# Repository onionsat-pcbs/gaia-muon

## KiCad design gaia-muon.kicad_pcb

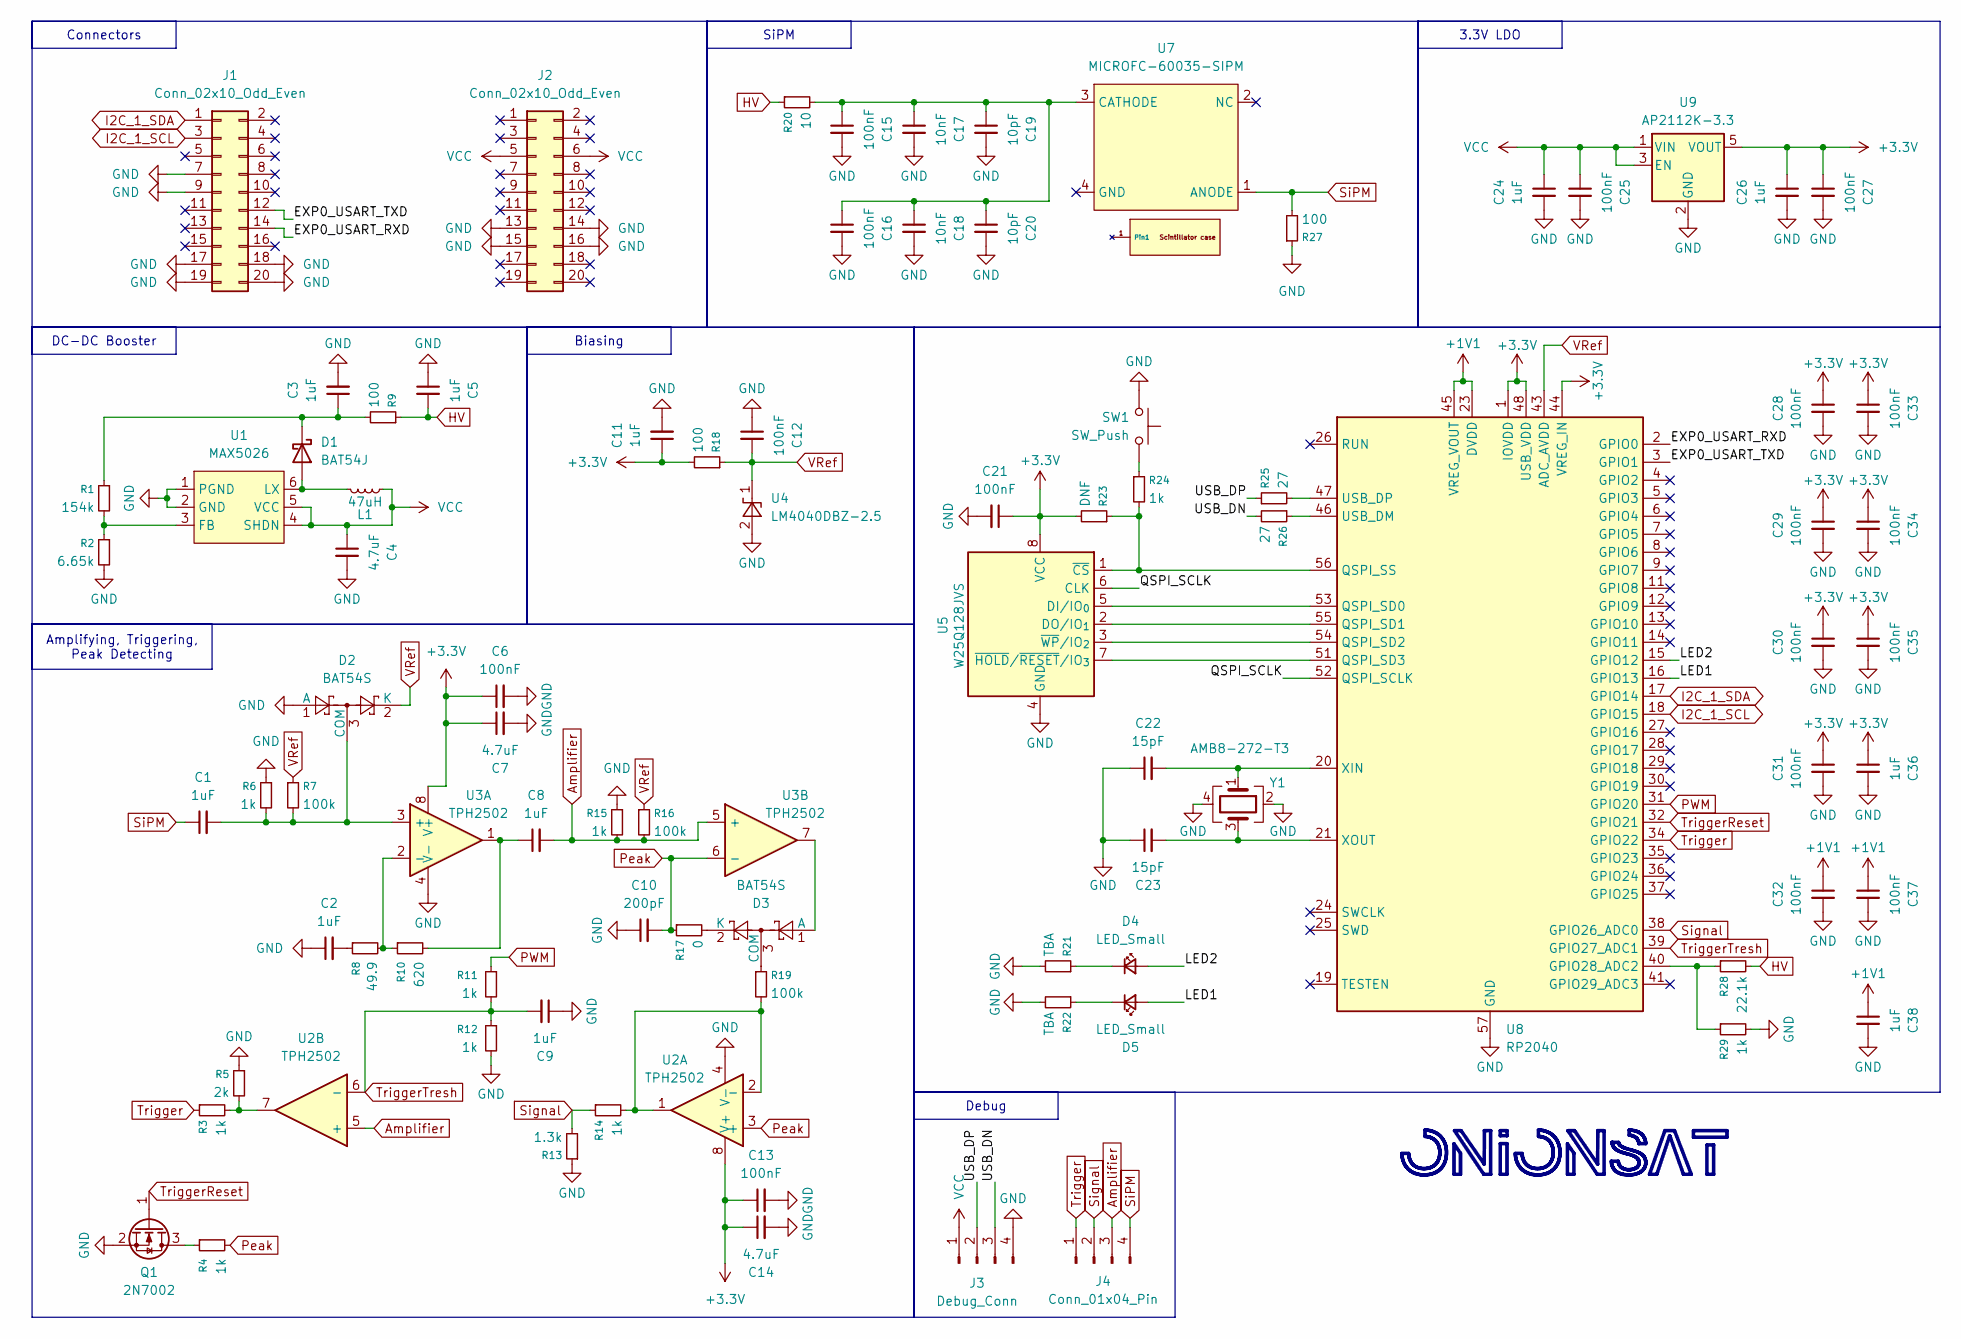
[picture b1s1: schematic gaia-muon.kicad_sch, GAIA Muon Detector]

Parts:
C1, C2, C3, C5, C8, C9, C11: 1uF; C_0805_2012Metric
C4: 4.7uF; C_0805_2012Metric
C6, C13, C28, C29, C30, C31, C32, C33, C34, C35, C37: 100nF; C_0402_1005Metric
C7, C14: 4.7uF; C_0402_1005Metric
C10: 200pF; C_0805_2012Metric
C12, C15, C16, C21: 100nF; C_0805_2012Metric
C17, C18: 10nF; C_0805_2012Metric
C19, C20: 10pF; C_0805_2012Metric
C22, C23: 15pF; C_0402_1005Metric
C24, C26: 1uF; C_0603_1608Metric
C25, C27: 100nF; C_0603_1608Metric
C36, C38: 1uF; C_0402_1005Metric
D1: BAT54J; D_SOD-323F
D2, D3: BAT54S; SOT-23
D4, D5: LED_Small; LED_0603_1608Metric
J1, J2: Conn_02x10_Odd_Even; Gaia_connector_2_4layer
J3: Debug_Conn; PinHeader_1x04_P2.54mm_Vertical
J4: Conn_01x04_Pin; PinHeader_1x04_P2.54mm_Vertical
L1: 47uH; L_0805_2012Metric
Q1: 2N7002; SOT-23
R1: 154k; R_0603_1608Metric
R2: 6.65k; R_0603_1608Metric
R3, R4, R6, R11, R12, R14, R15, R29: 1k; R_0805_2012Metric
R5: 2k; R_0805_2012Metric
R7, R16, R19: 100k; R_0805_2012Metric
R8: 49.9; R_0805_2012Metric
R9, R18, R27: 100; R_0805_2012Metric
R10: 620; R_0805_2012Metric
R13: 1.3k; R_0805_2012Metric
R17: 0; R_0805_2012Metric
R20: 10; R_0805_2012Metric
R21, R22: TBA; R_0402_1005Metric
R23: DNF; R_0402_1005Metric
R24: 1k; R_0402_1005Metric
R25, R26: 27; R_0402_1005Metric
R28: 22.1k; R_0805_2012Metric
SW1: SW_Push; KEY-SMD_L4.0-W3.0-LS4.9-1
U1: MAX5026; SOT-23-6
U2, U3: TPH2502; MSOP-8_3x3mm_P0.65mm
U4: LM4040DBZ-2.5; SOT-23
U5: W25Q128JVS; SOIC-8_5.3x5.3mm_P1.27mm
U6: scintillator-case
U7: MICROFC-60035-SIPM
U8: RP2040; QFN-56-1EP_7x7mm_P0.4mm_EP3.2x3.2mm
U9: AP2112K-3.3; SOT-23-5
Y1: AMB8-272-T3; Crystal_SMD_3225-4Pin_3.2x2.5mm

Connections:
+1V1: C32.1, C37.1, C38.1, U8.23 (DVDD), U8.45 (VREG_VOUT), U8.50 (DVDD)
+3.3V: C6.1, C7.1, C11.1, C13.1, C14.1, C21.1, C26.1, C27.1, C28.1, C29.1, C30.1, C31.1, C33.1, C34.1, C35.1, C36.1, R18.2, R23.2, U2.8 (V+), U3.8 (V+), U5.8 (VCC), U8.1 (IOVDD), U8.10 (IOVDD), U8.22 (IOVDD), U8.33 (IOVDD), U8.42 (IOVDD), U8.44 (VREG_IN), U8.48 (USB_VDD), U8.49 (IOVDD), U9.5 (VOUT)
/EXP0_USART_RXD: J1.14, U8.2 (GPIO0)
/EXP0_USART_TXD: J1.12, U8.3 (GPIO1)
/LED1: D5.2 (A), U8.16 (GPIO13)
/LED2: D4.2 (A), U8.15 (GPIO12)
/QSPI_SCLK: U5.6 (CLK), U8.52 (QSPI_SCLK)
/USB_DN: J3.3, R26.2
/USB_DP: J3.2, R25.1
Amplifier: C8.2, J4.3, R15.2, R16.2, U2.5 (+), U3.5 (+)
GND: C2.1, C3.2, C4.2, C5.1, C6.2, C7.2, C9.1, C10.1, C11.2, C12.1, C13.2, C14.2, C15.2, C16.2, C17.2, C18.2, C19.2, C20.2, C21.2, C22.1, C23.1, C24.2, C25.2, C26.2, C27.2, C28.2, C29.2, C30.2, C31.2, C32.2, C33.2, C34.2, C35.2, C36.2, C37.2, C38.2, D2.1 (A), J1.7, J1.9, J1.17, J1.18, J1.19, J1.20, J2.13, J2.14, J2.15, J2.16, J3.4, Q1.2 (S), R2.2, R5.1, R6.1, R12.2, R13.1, R15.1, R21.2, R22.2, R27.1, R29.2, SW1.2, U1.1 (PGND), U1.2 (GND), U2.4 (V-), U3.4 (V-), U4.2 (A), U5.4 (GND), U8.57 (GND), U9.2 (GND), Y1.2, Y1.4
HV: C5.2, R9.1, R20.1, R28.2
I2C_1_SCL: J1.3, U8.18 (GPIO15)
I2C_1_SDA: J1.1, U8.17 (GPIO14)
unnamed: C2.2, R8.1
unnamed: C8.1, R10.2, U3.1
unnamed: D1.2 (A), L1.1, U1.6 (LX)
unnamed: C3.1, D1.1 (K), R1.1, R9.2
unnamed: C1.2, D2.3 (COM), R6.2, R7.2, U3.3 (+)
unnamed: D3.1 (A), U3.7
unnamed: D3.3 (COM), R19.1
unnamed: D3.2 (K), R17.2
unnamed: D4.1 (K), R21.1
unnamed: D5.1 (K), R22.1
unnamed: Q1.3 (D), R4.1
unnamed: R3.2, R5.2, U2.7
unnamed: R24.1, SW1.1
unnamed: R1.2, R2.1, U1.3 (FB)
unnamed: R14.2, R19.2, U2.1, U2.2 (-)
unnamed: R8.2, R10.1, U3.2 (-)
unnamed: U5.5 (DI/IO_{0}), U8.53 (QSPI_SD0)
unnamed: U5.2 (DO/IO_{1}), U8.55 (QSPI_SD1)
unnamed: R23.1, R24.2, U5.1 (~CS), U8.56 (QSPI_SS)
unnamed: U5.7 (~HOLD/~RESET/IO_{3}), U8.51 (QSPI_SD3)
unnamed: U5.3 (~WP/IO_{2}), U8.54 (QSPI_SD2)
unnamed: C15.1, C16.1, C17.1, C18.1, C19.1, C20.1, R20.2, U7.3 (CATHODE)
unnamed: R28.1, R29.1, U8.40 (GPIO28_ADC2)
unnamed: R26.1, U8.46 (USB_DM)
unnamed: R25.2, U8.47 (USB_DP)
unnamed: C22.2, U8.20 (XIN), Y1.1
unnamed: C23.2, U8.21 (XOUT), Y1.3
PWM: R11.1, U8.31 (GPIO20)
Peak: C10.2, R4.2, R17.1, U2.3 (+), U3.6 (-)
SiPM: C1.1, J4.4, R27.2, U7.1 (ANODE)
Signal: J4.2, R13.2, R14.1, U8.38 (GPIO26_ADC0)
Trigger: J4.1, R3.1, U8.34 (GPIO22)
TriggerReset: Q1.1 (G), U8.32 (GPIO21)
TriggerTresh: C9.2, R11.2, R12.1, U2.6 (-), U8.39 (GPIO27_ADC1)
VCC: C4.1, C24.1, C25.1, J2.5, J2.6, J3.1, L1.2, U1.4 (SHDN), U1.5 (VCC), U9.1 (VIN), U9.3 (EN)
VRef: C12.2, D2.2 (K), R7.1, R16.1, R18.1, U4.1 (K), U8.43 (ADC_AVDD)

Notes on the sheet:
SiPM
3.3V LDO
Biasing
Connectors
Debug
Amplifying, Triggering, Peak Detecting
DC-DC Booster

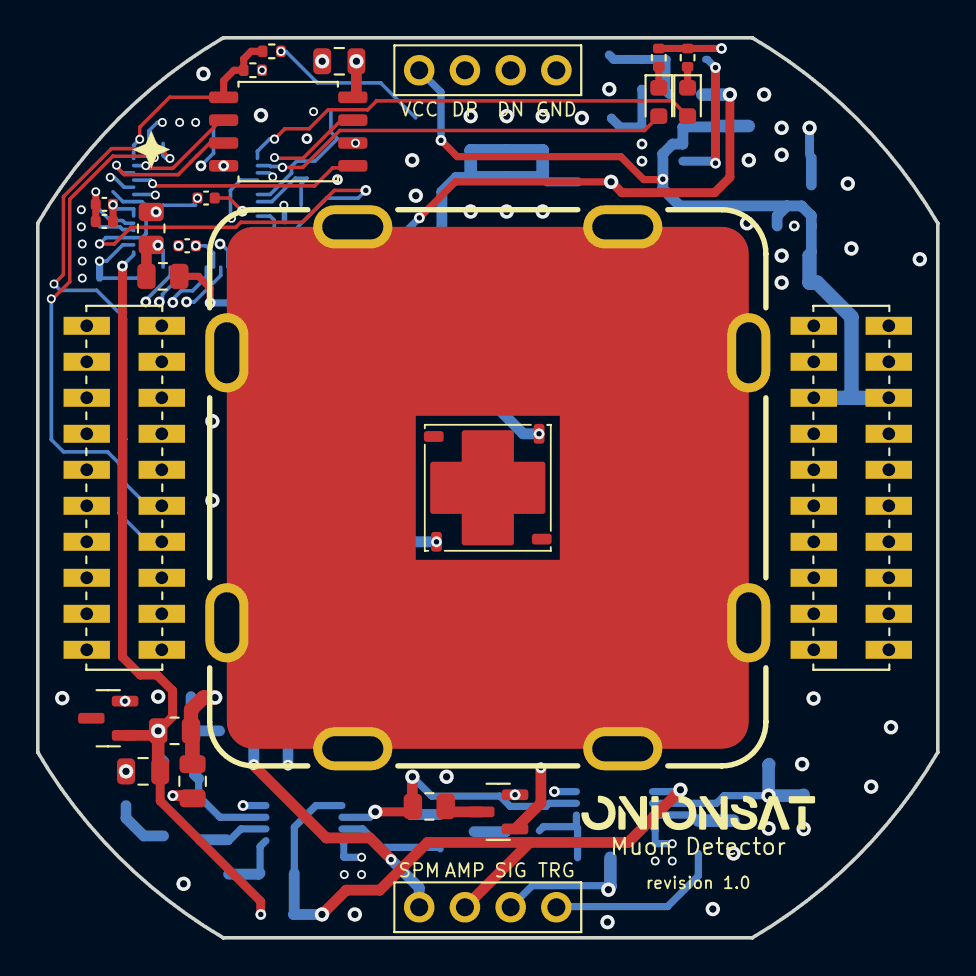
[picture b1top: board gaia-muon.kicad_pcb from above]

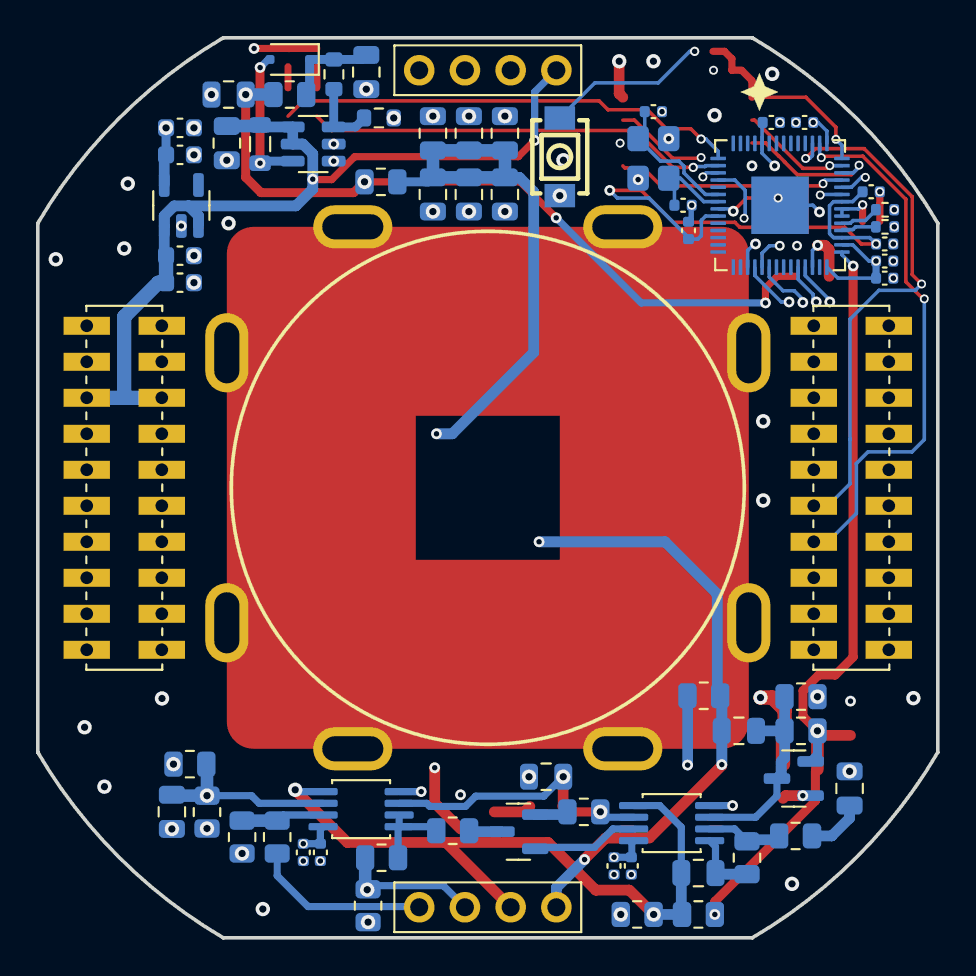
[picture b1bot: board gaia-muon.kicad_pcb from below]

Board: 6 copper layers, 50.0 x 50.0 mm, 89 parts (65 on the bottom side), 50 nets.

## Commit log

2025-10-12 creating schematic
2025-10-12 scintillator added
2025-10-13 scintillator case update
2025-10-14 placing components, start routing
2025-10-15 finish routing
2025-10-15 fix routing
2025-10-15 silkscreen cleanup
2025-10-15 removing 2 layers (8->6 layers)
2025-10-15 generating production file for JLC review
2025-10-16 Production start
2025-10-16 adding stitching vias
2026-01-07 fixing 3d models
